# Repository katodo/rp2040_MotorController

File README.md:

# rp2040_MotorController
rp2040 based MotorController

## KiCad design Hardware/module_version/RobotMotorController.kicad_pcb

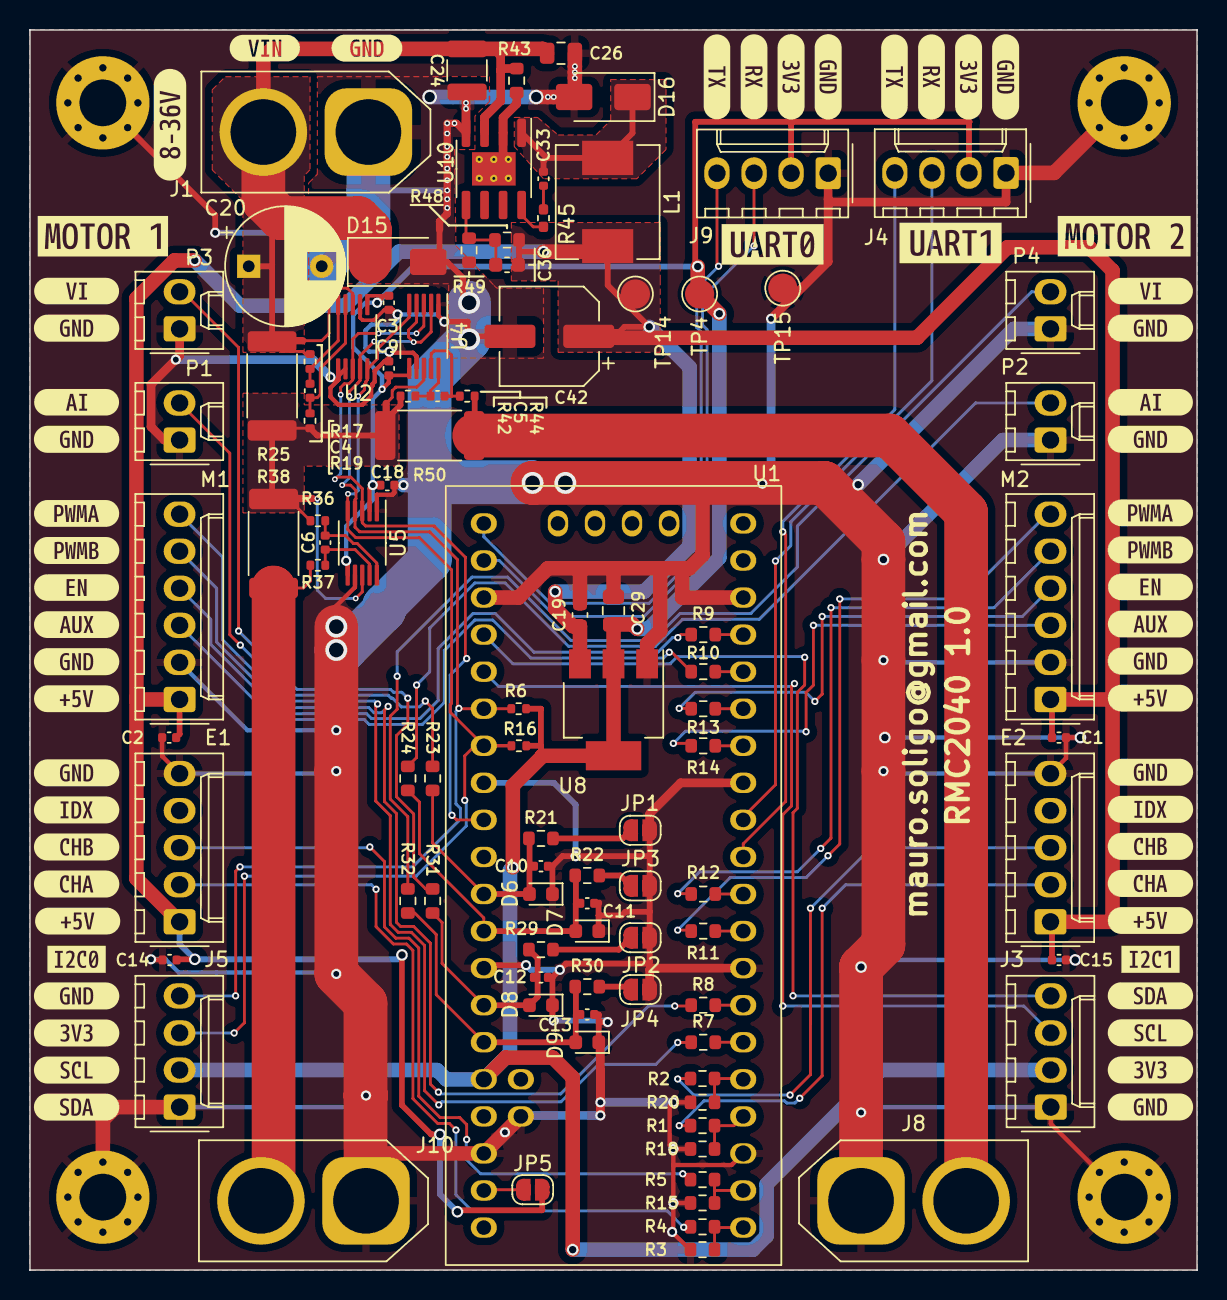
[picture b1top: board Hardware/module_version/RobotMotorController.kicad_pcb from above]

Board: 2 copper layers, 80.0 x 85.0 mm, 159 parts (0 on the bottom side), 67 nets.

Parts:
C1, C2, C3, C4, C5, C6, C9, C10, C11, C12, C13, C14, C15, C18, C33: 100n 16V; C_0402_1005Metric
C19: 1u; C_0603_1608Metric
C20: 47uF 50V; CP_Radial_D8.0mm_P5.00mm
C24: 4.7uF 100V; C_1210_3225Metric
C26: 100nF 100V; C_0805_2012Metric
C29: 10u; C_0805_2012Metric
C36: 47pf; C_0603_1608Metric
C42: 220uF 25V; CP_Elec_6.3x7.7
D6, D7, D8, D9: PESD5V0X1BCSFYL; D_0603_1608Metric
D15: SMAJ51A; D_SMA
D16: SS310; D_SMA
E1, E2: Molex_KK-254_AE-6410-05A_1x05_P2.54mm_Vertical
H1, H2, H3, H4: MOUNTING_HOLE; MountingHole_3.2mm_M3_Pad_Via
J1: XT60PW-F; AMASS_XT60-F_1x02_P7.20mm_Vertical
J3, J4, J5, J9: CONN_01x04; Molex_KK-254_AE-6410-04A_1x04_P2.54mm_Vertical
J8, J10: XT60PW-M; AMASS_XT60-M_1x02_P7.20mm_Vertical
JP1, JP2, JP3, JP4, JP5: Jumper_2_Open; SolderJumper-2_P1.3mm_Open_RoundedPad1.0x1.5mm
L1: 47uH; L_Chilisin_BMRB00060612
M1, M2: Molex_KK-254_AE-6410-06A_1x06_P2.54mm_Vertical
NT1, NT2, NT3: NetTie_2; NetTie-2_SMD_Pad0.5mm
P1, P2, P3, P4: Molex_KK-254_AE-6410-02A_1x02_P2.54mm_Vertical
R1, R2, R4, R5, R7, R8, R9, R10, R11, R12, R13, R14, R23, R24, R31, R32: 1K; R_0603_1608Metric
R3, R15, R18, R20: 1K96; R_0603_1608Metric
R6, R16: 1K/S4; R_0402_1005Metric
R17, R19, R36, R37, R42, R44: 10Ω/S4; R_0402_1005Metric
R21, R22, R29, R30: 1K87; R_0603_1608Metric
R25, R38, R50: 10mΩ 2W; R_2512_6332Metric_Pad1.40x3.35mm_HandSolder
R43: 50mΩ; R_0603_1608Metric
R45: 10Ω/S4; R_0402_1005Metric_Pad0.72x0.64mm_HandSolder
R48: 300k; R_0603_1608Metric
R49: 57.1K; R_0603_1608Metric
TP4, TP14, TP15: TestPoint; TestPoint_Pad_D2.0mm
U1: RP2040-rgb; rp2040_rgb
U2, U4, U5: INA237; VSSOP-10_3x3mm_P0.5mm
U8: TLV1117LV33DCYR; SOT-223-3_TabPin2
U10: TX4139; SOIC-8-1EP_3.9x4.9mm_P1.27mm_EP2.29x3mm_ThermalVias
kibuzzard-653D1AE4: G***; kibuzzard-653D1AE4
kibuzzard-653F53CF, kibuzzard-653F53CF#2: G***; kibuzzard-653F53CF
kibuzzard-653F53D5, kibuzzard-653F53D5#2: G***; kibuzzard-653F53D5
kibuzzard-653F53DB, kibuzzard-653F53DB#2: G***; kibuzzard-653F53DB
kibuzzard-653F53E4, kibuzzard-653F53E4#2: G***; kibuzzard-653F53E4
kibuzzard-653F53EC, kibuzzard-653F53EC#2, kibuzzard-653F53EC#3, kibuzzard-653F53EC#4, kibuzzard-653F53EC#5, kibuzzard-653F53EC#6: G***; kibuzzard-653F53EC
kibuzzard-653F53F2, kibuzzard-653F53F2#2, kibuzzard-653F53F2#3, kibuzzard-653F53F2#4: G***; kibuzzard-653F53F2
kibuzzard-653F55C0: G***; kibuzzard-653F55C0
kibuzzard-653F540C, kibuzzard-653F540C#2: G***; kibuzzard-653F540C
kibuzzard-653F541E, kibuzzard-653F541E#2: G***; kibuzzard-653F541E
kibuzzard-653F548C, kibuzzard-653F548C#2: G***; kibuzzard-653F548C
kibuzzard-653F5182: G***; kibuzzard-653F5182
kibuzzard-653F5379: G***; kibuzzard-653F5379
kibuzzard-653F5412, kibuzzard-653F5412#2: G***; kibuzzard-653F5412
kibuzzard-653F5418, kibuzzard-653F5418#2: G***; kibuzzard-653F5418
kibuzzard-653F5483, kibuzzard-653F5483#2: G***; kibuzzard-653F5483
kibuzzard-653F5495, kibuzzard-653F5495#2: G***; kibuzzard-653F5495
kibuzzard-654DCF3E, kibuzzard-654DCF3E#2: G***; kibuzzard-654DCF3E
kibuzzard-654DCF33, kibuzzard-654DCF33#2: G***; kibuzzard-654DCF33
kibuzzard-654DCF59, kibuzzard-654DCF59#2: G***; kibuzzard-654DCF59
kibuzzard-654DCFB0, kibuzzard-654DCFB0#2: G***; kibuzzard-654DCFB0
kibuzzard-654DCFBA, kibuzzard-654DCFBA#2: G***; kibuzzard-654DCFBA
kibuzzard-654DCFC5, kibuzzard-654DCFC5#2: G***; kibuzzard-654DCFC5
kibuzzard-654DCFCD, kibuzzard-654DCFCD#2: G***; kibuzzard-654DCFCD
kibuzzard-655CCB55: G***; kibuzzard-655CCB55
kibuzzard-655CCBF1: G***; kibuzzard-655CCBF1
kibuzzard-6394D9EA: G***; kibuzzard-6394D9EA
kibuzzard-6576B604: G***; kibuzzard-6576B604
kibuzzard-6576B615: G***; kibuzzard-6576B615

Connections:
+3V3: C3.1, C9.1, C18.1, C29.1, J3.2, J4.2, J5.2, J9.2, R6.1, R16.1, TP4.1, U1.36 (3V3), U2.6 (VS), U4.6 (VS), U5.2 (A0), U5.6 (VS), U8.2 (VO)
+5V: C1.1, C2.1, C14.1, C15.1, C19.1, C36.1, C42.1, E1.1, E2.1, JP5.2 (B), L1.2, M1.1, M2.1, R48.2, TP14.1, U8.3 (VI)
/Analog/I1: P1.2, R23.1
/Analog/I2: P2.2, R24.1
/Analog/V1: P3.2, R31.1
/Analog/V2: P4.2, R32.1
/PowerOut/Vout1: J8.2 (+), R44.2, R50.1
/PowerOut/Vout2: J10.2 (+), R37.2, R38.1
/Supply and Power/BS: R45.1, U10.8 (BS)
/Supply and Power/FB: C36.2, R48.1, R49.2, U10.5 (FB)
/Supply and Power/SW: C33.1, D16.1 (K), L1.1, U10.1 (SW)
ADC_M1_CURRENT: C10.1, D6.2 (A2), R21.1, R23.2, U1.31 (GP26)
ADC_M1_VOLTAGE: C12.1, D8.2 (A2), R29.1, R31.2, U1.34 (GP28)
ADC_M2_CURRENT: C11.1, D7.2 (A2), R22.1, R24.2, U1.32 (GP27)
ADC_M2_VOLTAGE: C13.1, D9.2 (A2), R30.1, R32.2, U1.35 (GP29)
AUX1: M1.3, R10.1
AUX2: M2.3, R14.1
BATT_OUT: NT1.2, NT2.2, R19.2, R25.1, R36.2, R38.2, R42.2, R50.2
E1_CHA: R3.2, R4.2, U1.1 (GP0)
E1_CHA_OUT: E1.2, R4.1
E1_CHB: R5.2, R15.2, U1.2 (GP1)
E1_CHB_OUT: E1.3, R5.1
E2_CHA: R1.2, R18.2, U1.4 (GP2)
E2_CHA_OUT: E2.2, R1.1
E2_CHB: R2.2, R20.2, U1.5 (GP3)
E2_CHB_OUT: E2.3, R2.1
EN1: M1.4, R9.1
EN2: M2.4, R13.1
GND: C1.2, C2.2, C3.2, C9.2, C10.2, C11.2, C12.2, C13.2, C14.2, C15.2, C18.2, C19.2, C20.2, C24.2, C26.2, C29.2, C42.2, D6.1 (A1), D7.1 (A1), D8.1 (A1), D9.1 (A1), D15.2 (A2), D16.2 (A), E1.5, E2.5, H1.1, H2.1, H3.1, H4.1, J1.1 (-), J3.1, J4.1, J5.1, J8.1 (-), J9.1, J10.1 (-), JP1.2 (B), JP2.2 (B), JP3.2 (B), JP4.2 (B), M1.2, M2.2, P1.1, P2.1, P3.1, P4.1, R3.1, R15.1, R18.1, R20.1, R49.1, TP15.1, U1.3 (GND), U1.8 (GND), U1.13 (GND), U1.18 (GND), U1.23 (GND), U1.28 (GND), U1.33 (GND), U1.38 (GND), U1.45 (GND), U2.1 (A1), U2.2 (A0), U2.7 (GND), U4.1 (A1), U4.7 (GND), U5.1 (A1), U5.7 (GND), U8.1 (GND), U10.4 (GND)
I2C0-ALERT: U1.29 (GP22), U2.3 (ALERT), U4.3 (ALERT), U5.3 (ALERT)
I2C0-SCL: J5.3, R16.2, U1.27 (GP21), U2.5 (SCL), U4.5 (SCL), U5.5 (SCL)
I2C0-SDA: J5.4, R6.2, U1.26 (GP20), U2.4 (SDA), U4.2 (A0), U4.4 (SDA), U5.4 (SDA)
I2C1-SCL: J3.3, U1.25 (GP19)
I2C1-SDA: J3.4, U1.24 (GP18)
MOT1_AUX: R10.2, U1.16 (GP12)
MOT1_EN: R9.2, U1.17 (GP13)
MOT1_N: R8.2, U1.7 (GP5)
MOT1_P: R7.2, U1.6 (GP4)
MOT2_AUX: R14.2, U1.14 (GP10)
MOT2_EN: R13.2, U1.15 (GP11)
MOT2_N: R12.2, U1.10 (GP7)
MOT2_P: R11.2, U1.9 (GP6)
unnamed: C33.2, R45.2
unnamed: JP1.1 (A), R21.2
unnamed: JP2.1 (A), R29.2
unnamed: JP3.1 (A), R22.2
unnamed: JP4.1 (A), R30.2
unnamed: JP5.1 (A), U1.39 (VIN)
unnamed: R43.1, U10.2 (ILIM), U10.9 (ILIM)
unnamed: C4.2, R17.1, U2.10 (IN+)
unnamed: C4.1, R19.1, U2.9 (IN-)
unnamed: NT3.1, U2.8 (VBUS)
unnamed: C5.2, R42.1, U4.10 (IN+)
unnamed: C5.1, R44.1, U4.9 (IN-)
unnamed: NT2.1, U4.8 (VBUS)
unnamed: C6.2, R36.1, U5.10 (IN+)
unnamed: C6.1, R37.1, U5.9 (IN-)
unnamed: NT1.1, U5.8 (VBUS)
PWMA1: M1.6, R7.1
PWMA2: M2.6, R11.1
PWMB1: M1.5, R8.1
PWMB2: M2.5, R12.1
UART0_RX: J9.3, U1.22 (GP17)
UART0_TX: J9.4, U1.21 (GP16)
UART1_RX: J4.3, U1.12 (GP9)
UART1_TX: J4.4, U1.11 (GP8)
Vdrive: C20.1, C24.1, C26.1, D15.1 (A1), J1.2 (+), NT3.2, R17.2, R25.2, R43.2, U10.3 (VIN)

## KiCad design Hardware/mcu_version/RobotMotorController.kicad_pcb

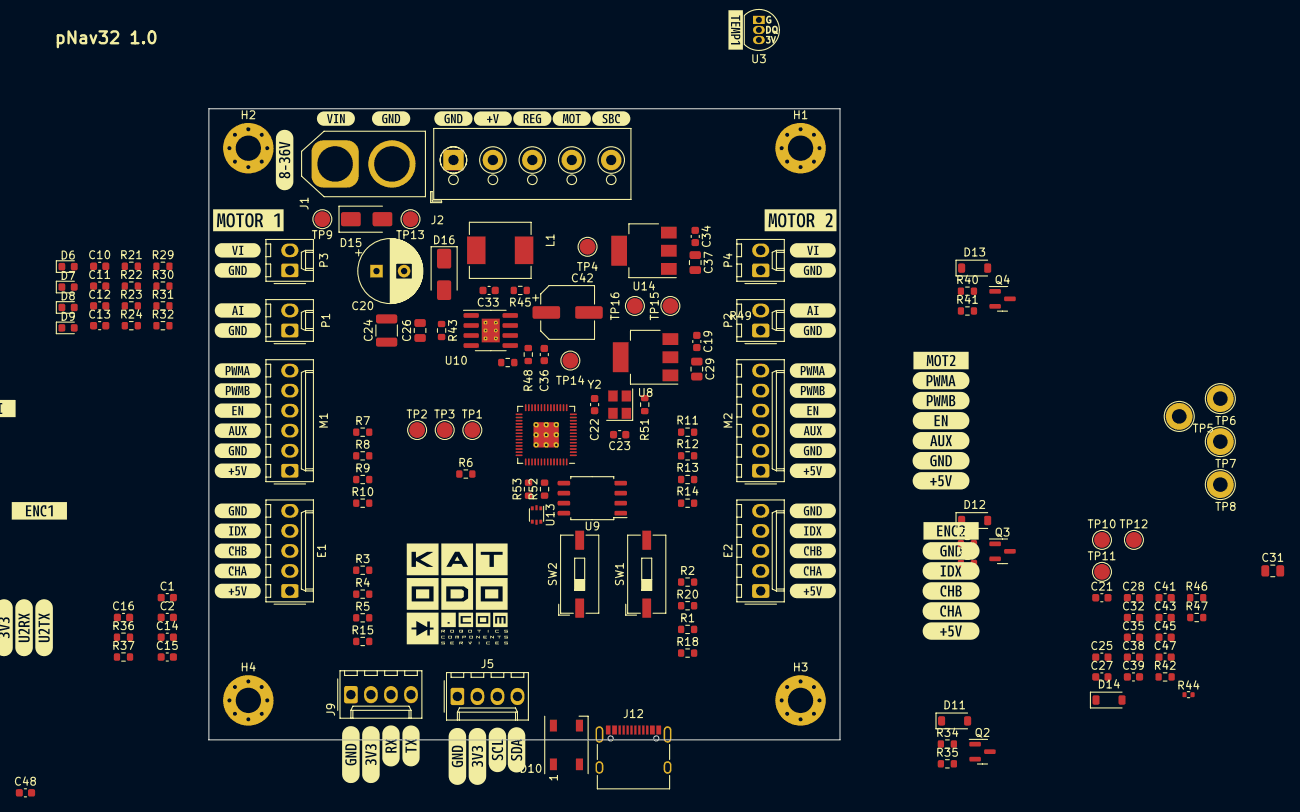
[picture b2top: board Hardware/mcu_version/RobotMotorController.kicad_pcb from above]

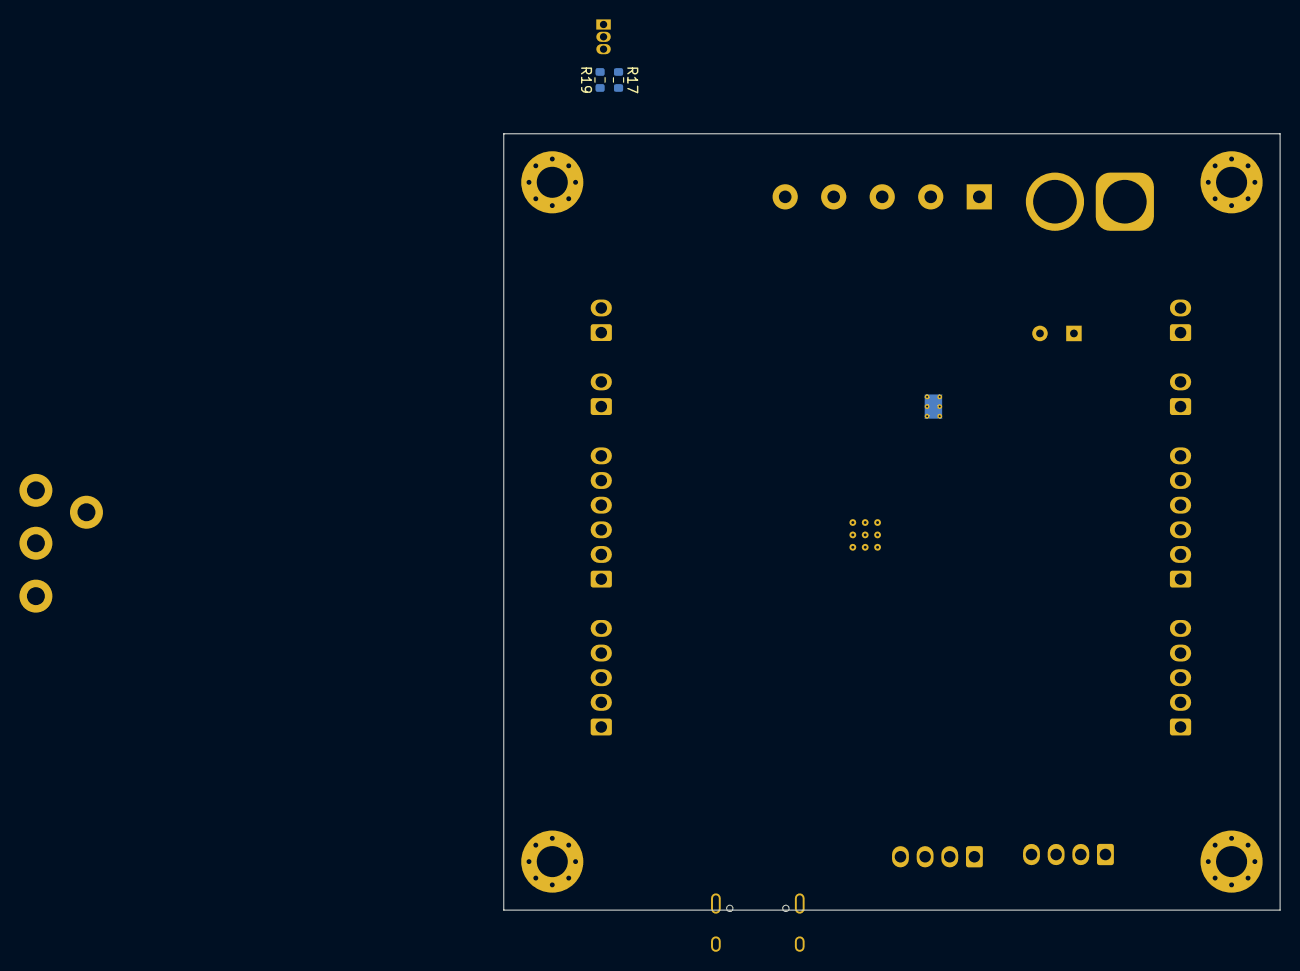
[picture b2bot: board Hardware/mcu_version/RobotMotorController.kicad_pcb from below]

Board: 2 copper layers, 80.0 x 80.0 mm, 212 parts (2 on the bottom side), 77 nets, no tracks yet.

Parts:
C1, C2, C10, C11, C12, C13, C14, C15, C16, C21, C25, C27, C32, C33, C35, C38, C41, C43, C45, C47, C48: 100n; C_0603_1608Metric
C19, C28, C34, C39: 1u; C_0603_1608Metric
C20: 47uF 63V solid; CP_Radial_D8.0mm_P3.50mm
C22, C23: 20p; C_0603_1608Metric
C24: 4.7uF 100V; C_1210_3225Metric
C26: 100nF 100V; C_0805_2012Metric
C29, C31, C37: 10u; C_0805_2012Metric
C36: 47pf; C_0603_1608Metric
C42: 220uF 25V; CP_Elec_6.3x7.7
D6, D7, D8, D9: PESD5V0X1BCSFYL; D_0603_1608Metric
D10: WS2812B; LED_WS2812B_PLCC4_5.0x5.0mm_P3.2mm
D11, D12, D13: 1N4148W; D_SOD-123
D14: B5819W SL; D_SOD-123
D15: SMAJ51A; D_SMA
D16: SS310; D_SMA
E1, E2: Molex_KK-254_AE-6410-05A_1x05_P2.54mm_Vertical
H1, H2, H3, H4: MOUNTING_HOLE; MountingHole_3.2mm_M3_Pad_Via
J1: Power Input; AMASS_XT60-F_1x02_P7.20mm_Vertical
J2: Conn_01x05; DG300-5.0-05P-13
J5, J9: CONN_01x04; Molex_KK-254_AE-6410-04A_1x04_P2.54mm_Vertical
J12: CPU1 USB; USB_C_Receptacle_XKB_U262-16XN-4BVC11
L1: 47uH; L_Chilisin_BMRB00060612
M1, M2: Molex_KK-254_AE-6410-06A_1x06_P2.54mm_Vertical
P1, P2, P3, P4: Molex_KK-254_AE-6410-02A_1x02_P2.54mm_Vertical
Q2, Q3, Q4: BSS138; SOT-23
R1, R2, R4, R5, R7, R8, R9, R10, R11, R12, R13, R14, R17, R19, R23, R24, R31, R32: 1K; R_0603_1608Metric
R3, R15, R18, R20: 1K96; R_0603_1608Metric
R6, R42, R51: 1.1k; R_0603_1608Metric
R21, R22, R29, R30, R35, R37, R39, R41: 10K; R_0603_1608Metric
R34, R38, R40: 100R; R_0603_1608Metric
R36: 100K; R_0603_1608Metric
R43: 50mΩ; R_0603_1608Metric
R44: DNS; R_0402_1005Metric
R45: 10Ω; R_0603_1608Metric
R46, R47: 5.1k; R_0603_1608Metric
R48: 300k; R_0603_1608Metric
R49: 57.1K; R_0603_1608Metric
R52, R53: 27; R_0603_1608Metric
SW1, SW2: SW_MEC_5G; SW_DIP_SPSTx01_Slide_9.78x4.72mm_W8.61mm_P2.54mm
TP1, TP2, TP3, TP4, TP9, TP10, TP11, TP12, TP13, TP14, TP15, TP16: TestPoint; TestPoint_Pad_D2.0mm
TP5, TP6, TP7, TP8: TESTPAD; TestPoint_Loop_D2.50mm_Drill1.85mm
U3: #DS18B20; TO-92_Inline
U8, U14: TLV1117LV33DCYR; SOT-223-3_TabPin2
U9: W25Q128JVSIQ; SOIC-8_5.23x5.23mm_P1.27mm
U10: TX4139; SOIC-8-1EP_3.9x4.9mm_P1.27mm_EP2.29x3mm_ThermalVias
U11: RP2040; RP2040-QFN-56
U13: USBLC6-2P6; SOT-666
Y2: 12MHz; Crystal_SMD_3225-4Pin_3.2x2.5mm
kibuzzard-63AAD7A3: G***; kibuzzard-63AAD7A3
kibuzzard-63AAD294: G***; kibuzzard-63AAD294
kibuzzard-653A01FC: G***; kibuzzard-653A01FC
kibuzzard-653A021C: G***; kibuzzard-653A021C
kibuzzard-653A0202: G***; kibuzzard-653A0202
kibuzzard-653A0212: G***; kibuzzard-653A0212
kibuzzard-653D1AE4, kibuzzard-653D1AE4#2: G***; kibuzzard-653D1AE4
kibuzzard-653D1AEE: G***; kibuzzard-653D1AEE
kibuzzard-653D1AF5: G***; kibuzzard-653D1AF5
kibuzzard-653D1B0A: G***; kibuzzard-653D1B0A
kibuzzard-653D1B23: G***; kibuzzard-653D1B23
kibuzzard-653F53CF, kibuzzard-653F53CF#2: G***; kibuzzard-653F53CF
kibuzzard-653F53D5, kibuzzard-653F53D5#2: G***; kibuzzard-653F53D5
kibuzzard-653F53DB, kibuzzard-653F53DB#2: G***; kibuzzard-653F53DB
kibuzzard-653F53E4, kibuzzard-653F53E4#2: G***; kibuzzard-653F53E4
kibuzzard-653F53EC, kibuzzard-653F53EC#2, kibuzzard-653F53EC#3, kibuzzard-653F53EC#4: G***; kibuzzard-653F53EC
kibuzzard-653F53F2, kibuzzard-653F53F2#2, kibuzzard-653F53F2#3, kibuzzard-653F53F2#4: G***; kibuzzard-653F53F2
kibuzzard-653F55C0: G***; kibuzzard-653F55C0
kibuzzard-653F540C, kibuzzard-653F540C#2: G***; kibuzzard-653F540C
kibuzzard-653F541E, kibuzzard-653F541E#2: G***; kibuzzard-653F541E
kibuzzard-653F548C, kibuzzard-653F548C#2: G***; kibuzzard-653F548C
kibuzzard-653F5182: G***; kibuzzard-653F5182
kibuzzard-653F5379: G***; kibuzzard-653F5379
kibuzzard-653F5412, kibuzzard-653F5412#2: G***; kibuzzard-653F5412
kibuzzard-653F5418, kibuzzard-653F5418#2: G***; kibuzzard-653F5418
kibuzzard-653F5483, kibuzzard-653F5483#2: G***; kibuzzard-653F5483
kibuzzard-653F5495, kibuzzard-653F5495#2: G***; kibuzzard-653F5495
kibuzzard-6394D4E3, kibuzzard-6394D4E3#2, kibuzzard-6394D4E3#3, kibuzzard-6394D4E3#4: G***; kibuzzard-6394D4E3
kibuzzard-6394D4F3, kibuzzard-6394D4F3#2, kibuzzard-6394D4F3#3, kibuzzard-6394D4F3#4: G***; kibuzzard-6394D4F3
kibuzzard-6394D9EA: G***; kibuzzard-6394D9EA
kibuzzard-6394D52A: G***; kibuzzard-6394D52A
kibuzzard-6394D57A: G***; kibuzzard-6394D57A
kibuzzard-6394D524: G***; kibuzzard-6394D524
kibuzzard-6394D572: G***; kibuzzard-6394D572
kibuzzard-63934BF7: G***; kibuzzard-63934BF7
kibuzzard-639345B8: G***; kibuzzard-639345B8
kibuzzard-6393426E: G***; kibuzzard-6393426E
kibuzzard-6393456C: G***; kibuzzard-6393456C
kibuzzard-6393459E: G***; kibuzzard-6393459E
kibuzzard-6393473F: G***; kibuzzard-6393473F
kibuzzard-63934268: G***; kibuzzard-63934268
kibuzzard-63934273, kibuzzard-63934273#2: G***; kibuzzard-63934273
kibuzzard-63934574: G***; kibuzzard-63934574
kibuzzard-63934735: G***; kibuzzard-63934735
kibuzzard-63934749: G***; kibuzzard-63934749
kibuzzard-63934750: G***; kibuzzard-63934750
kibuzzard-63934760: G***; kibuzzard-63934760
kibuzzard-63934774: G***; kibuzzard-63934774

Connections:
+1V1: C25.1, C27.1, C28.1, U11.23 (DVDD), U11.45 (VREG_VOUT), U11.50 (DVDD)
+3.3VA: C32.1, C37.1, TP16.1, U11.43 (ADC_AVDD), U14.2 (VO)
+3V3: C21.1, C29.1, C31.1, C35.1, C38.1, C39.1, C41.1, C43.1, C45.1, C47.1, C48.1, D10.1 (VDD), J5.2, J9.2, R6.1, R19.2, R44.1, TP7.1 (TP), TP15.1, U3.3 (VDD), U8.2 (VO), U9.8 (VCC), U11.1 (IOVDD), U11.10 (IOVDD), U11.22 (IOVDD), U11.33 (IOVDD), U11.42 (IOVDD), U11.44 (VREG_IN), U11.48 (USB_VDD), U11.49 (IOVDD)
+5V: C1.1, C2.1, C14.1, C15.1, C19.1, C34.1, C36.1, C42.1, D14.1 (K), E1.1, E2.1, L1.2, M1.1, M2.1, R48.2, TP8.1 (TP), TP14.1, U8.3 (VI), U14.3 (VI)
/QSPI_SCLK: U9.6 (CLK), U11.52 (QSPI_SCLK)
/QSPI_SD0: U9.5 (DI(IO0)), U11.53 (QSPI_SD0)
/QSPI_SD1: U9.2 (DO(IO1)), U11.55 (QSPI_SD1)
/QSPI_SD2: U9.3 (IO2), U11.54 (QSPI_SD2)
/QSPI_SD3: U9.7 (IO3), U11.51 (QSPI_SD3)
/QSPI_SS: R42.2, R44.2, U9.1 (~CS), U11.56 (QSPI_SS)
/SWCLK: TP2.1, U11.24 (SWCLK)
/SWD: TP3.1, U11.25 (SWD)
/Supply and Power/BS: R45.1, U10.8 (BS)
/Supply and Power/FB: C36.2, R48.1, R49.2, U10.5 (FB)
/Supply and Power/O_MOT: D12.2 (A), J2.4, Q3.3 (D)
/Supply and Power/O_REG: D13.2 (A), J2.3, Q4.3 (D)
/Supply and Power/O_SBC: D11.2 (A), J2.5, Q2.3 (D)
/Supply and Power/SW: C33.1, D16.1 (K), L1.1, U10.1 (SW)
/USB_D+: J12.A6 (D+), J12.B6 (D+), TP12.1, U13.6 (I/O1)
/USB_D-: J12.A7 (D-), J12.B7 (D-), TP11.1, U13.4 (I/O2)
/USB_DN: R53.2, U11.46 (USB_DM)
/USB_DP: R52.2, U11.47 (USB_DP)
/~RESET: R6.2, SW2.2, U11.26 (RUN)
/~USB_BOOT: R42.1, SW1.2
ADC_M1_CURRENT: C10.1, D6.2 (A2), R21.1, R23.2, U11.38 (GPIO26_ADC0)
ADC_M1_VOLTAGE: C12.1, D8.2 (A2), R29.1, R31.2, U11.40 (GPIO28_ADC2)
ADC_M2_CURRENT: C11.1, D7.2 (A2), R22.1, R24.2, U11.39 (GPIO27_ADC1)
ADC_M2_VOLTAGE: C13.1, D9.2 (A2), R30.1, R32.2, U11.41 (GPIO29_ADC3)
ADC_MAIN_SUPPLY: C16.1, R36.2, R37.1
AUX1: M1.3, R10.1
AUX2: M2.3, R14.1
E1_CHA: E1.2, R3.2, R4.1, R4.2, U11.2 (GPIO0)
E1_CHB: E1.3, R5.1, R5.2, R15.2, U11.3 (GPIO1)
E2_CHA: E2.2, R1.1, R1.2, R18.2, U11.4 (GPIO2)
E2_CHB: E2.3, R2.1, R2.2, R20.2, U11.5 (GPIO3)
EN1: M1.4, R9.1
EN2: M2.4, R13.1
GND: C1.2, C2.2, C10.2, C11.2, C12.2, C13.2, C14.2, C15.2, C16.2, C19.2, C20.2, C21.2, C22.2, C23.2, C24.2, C25.2, C26.2, C27.2, C28.2, C29.2, C31.2, C32.2, C34.2, C35.2, C37.2, C38.2, C39.2, C41.2, C42.2, C43.2, C45.2, C47.2, C48.2, D6.1 (A1), D7.1 (A1), D8.1 (A1), D9.1 (A1), D10.3 (VSS), D15.2 (A2), D16.2 (A), E1.5, E2.5, H1.1, H2.1, H3.1, H4.1, J1.2, J2.1, J5.1, J9.1, J12.A1 (GND), J12.A12 (GND), J12.B1 (GND), J12.B12 (GND), J12.S1 (SHIELD), M1.2, M2.2, P1.1, P2.1, P3.1, P4.1, Q2.2 (S), Q3.2 (S), Q4.2 (S), R3.1, R15.1, R18.1, R20.1, R21.2, R22.2, R29.2, R30.2, R35.2, R37.2, R39.2, R41.2, R46.1, R47.2, R49.1, SW1.1, SW2.1, TP1.1, TP4.1, TP5.1 (TP), TP6.1 (TP), TP13.1, U3.1 (GND), U8.1 (GND), U9.4 (GND), U10.4 (GND), U11.19 (TESTEN), U11.57 (GND), U13.2 (GND), U14.1 (GND), Y2.2, Y2.4
I2C-SCL: J5.3, U11.32 (GPIO21)
I2C-SDA: J5.4, U11.31 (GPIO20)
LED_DATA: D10.4 (DIN), U11.29 (GPIO18)
MOT1_AUX: R10.2, U11.11 (GPIO8)
MOT1_EN: R9.2, U11.12 (GPIO9)
MOT1_N: R8.2, U11.7 (GPIO5)
MOT1_P: R7.2, U11.6 (GPIO4)
MOT2_AUX: R14.2, U11.13 (GPIO10)
MOT2_EN: R13.2, U11.14 (GPIO11)
MOT2_N: R12.2, U11.9 (GPIO7)
MOT2_P: R11.2, U11.8 (GPIO6)
unnamed: C23.1, R51.2, Y2.1
unnamed: C33.2, R45.2
unnamed: J12.A5 (CC1), R46.2
unnamed: J12.B5 (CC2), R47.1
unnamed: P1.2, R23.1
unnamed: P2.2, R24.1
unnamed: P3.2, R31.1
unnamed: P4.2, R32.1
unnamed: Q2.1 (G), R34.1, R35.1
unnamed: Q3.1 (G), R38.1, R39.1
unnamed: Q4.1 (G), R40.1, R41.1
unnamed: R43.1, U10.2 (ILIM), U10.9 (ILIM)
unnamed: R52.1, U13.1 (I/O1)
unnamed: R53.1, U13.3 (I/O2)
unnamed: R17.1, R19.1, U3.2 (DQ)
unnamed: C22.1, U11.20 (XIN), Y2.3
unnamed: R51.1, U11.21 (XOUT)
PWMA1: M1.6, R7.1
PWMA2: M2.6, R11.1
PWMB1: M1.5, R8.1
PWMB2: M2.5, R12.1
PWR-REG-EN: R40.2, U11.18 (GPIO15)
PWR_MOT_EN: R34.2, U11.16 (GPIO13)
PWR_SBC_EN: R38.2, U11.17 (GPIO14)
UART_RX: J9.3, U11.28 (GPIO17)
UART_TX: J9.4, U11.27 (GPIO16)
VBUS2: D14.2 (A), J12.A4 (VBUS), J12.A9 (VBUS), J12.B4 (VBUS), J12.B9 (VBUS), TP10.1, U13.5 (VBUS)
Vdrive: C20.1, C24.1, C26.1, D11.1 (K), D12.1 (K), D13.1 (K), D15.1 (A1), J1.1, J2.2, R36.1, R43.2, TP9.1, U10.3 (VIN)

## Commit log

2023-10-26 work in progress...
2023-11-10 Initial work on a semplified version with usage of RP2040 modules
2023-11-10 Work in progress on rm2040 module version.
2023-12-12 Rev 0.9, ready to check...
2024-01-19 backup
2024-01-22 Final version - Production 22/01/2024
